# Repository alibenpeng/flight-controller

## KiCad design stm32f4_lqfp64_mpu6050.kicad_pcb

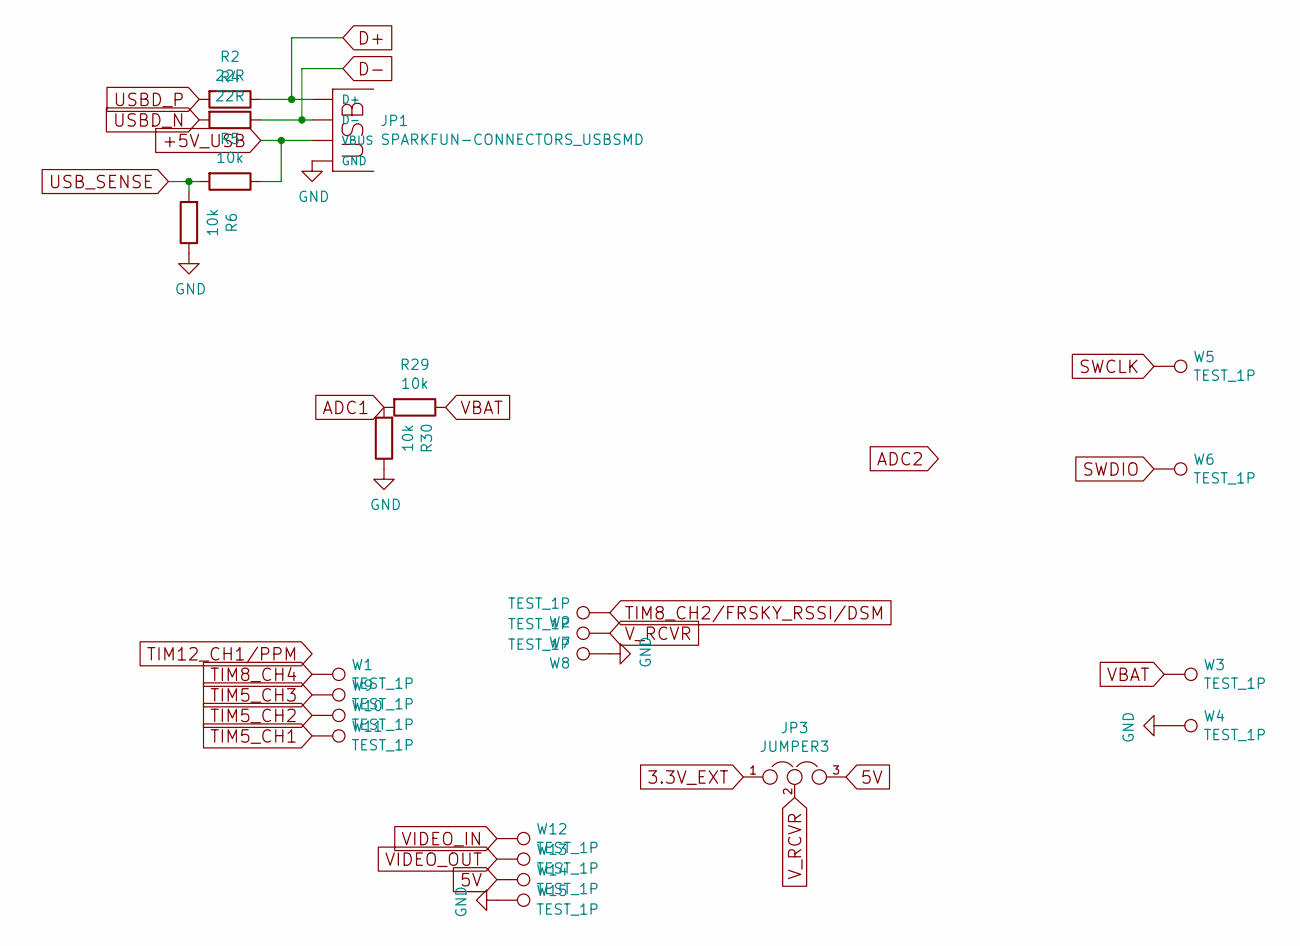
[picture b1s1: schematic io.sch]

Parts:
JP1: SPARKFUN-CONNECTORS_USBSMD; micro_usb
JP3: JUMPER3; SPARKFUN-PASSIVES_PAD-JUMPER-3-2OF3_NC_BY_PASTE_YES_SILK_FU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
R2, R4: 22R; R_0402
R5, R6, R29, R30: 10k; R_0402
W1, W2, W7, W8, W9, W10, W11, W12, W13, W14, W15: TEST_1P; pad_2x1.5mm
W3, W4: TEST_1P; battery_pad
W5, W6: TEST_1P; pad_round_1mm

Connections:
3.3V_EXT: JP3.1; also elsewhere on the board
5V: JP3.3, W14.1; also elsewhere on the board
+5V_USB: JP1.VBUS, R5.1; also elsewhere on the board
ADC1: R29.2, R30.2; also elsewhere on the board
D+: JP1.D+, R2.1
D-: JP1.D-, R4.1
SWCLK: W5.1; also elsewhere on the board
SWDIO: W6.1; also elsewhere on the board
TIM5_CH1: W11.1; also elsewhere on the board
TIM5_CH2: W10.1; also elsewhere on the board
TIM5_CH3: W9.1; also elsewhere on the board
TIM8_CH2/FRSKY_RSSI/DSM: W2.1; also elsewhere on the board
TIM8_CH4: W1.1; also elsewhere on the board
USBD_N: R4.2; also elsewhere on the board
USBD_P: R2.2; also elsewhere on the board
USB_SENSE: R5.2, R6.2; also elsewhere on the board
VIDEO_IN: W12.1; also elsewhere on the board
VIDEO_OUT: W13.1; also elsewhere on the board
V_RCVR: JP3.2, W7.1

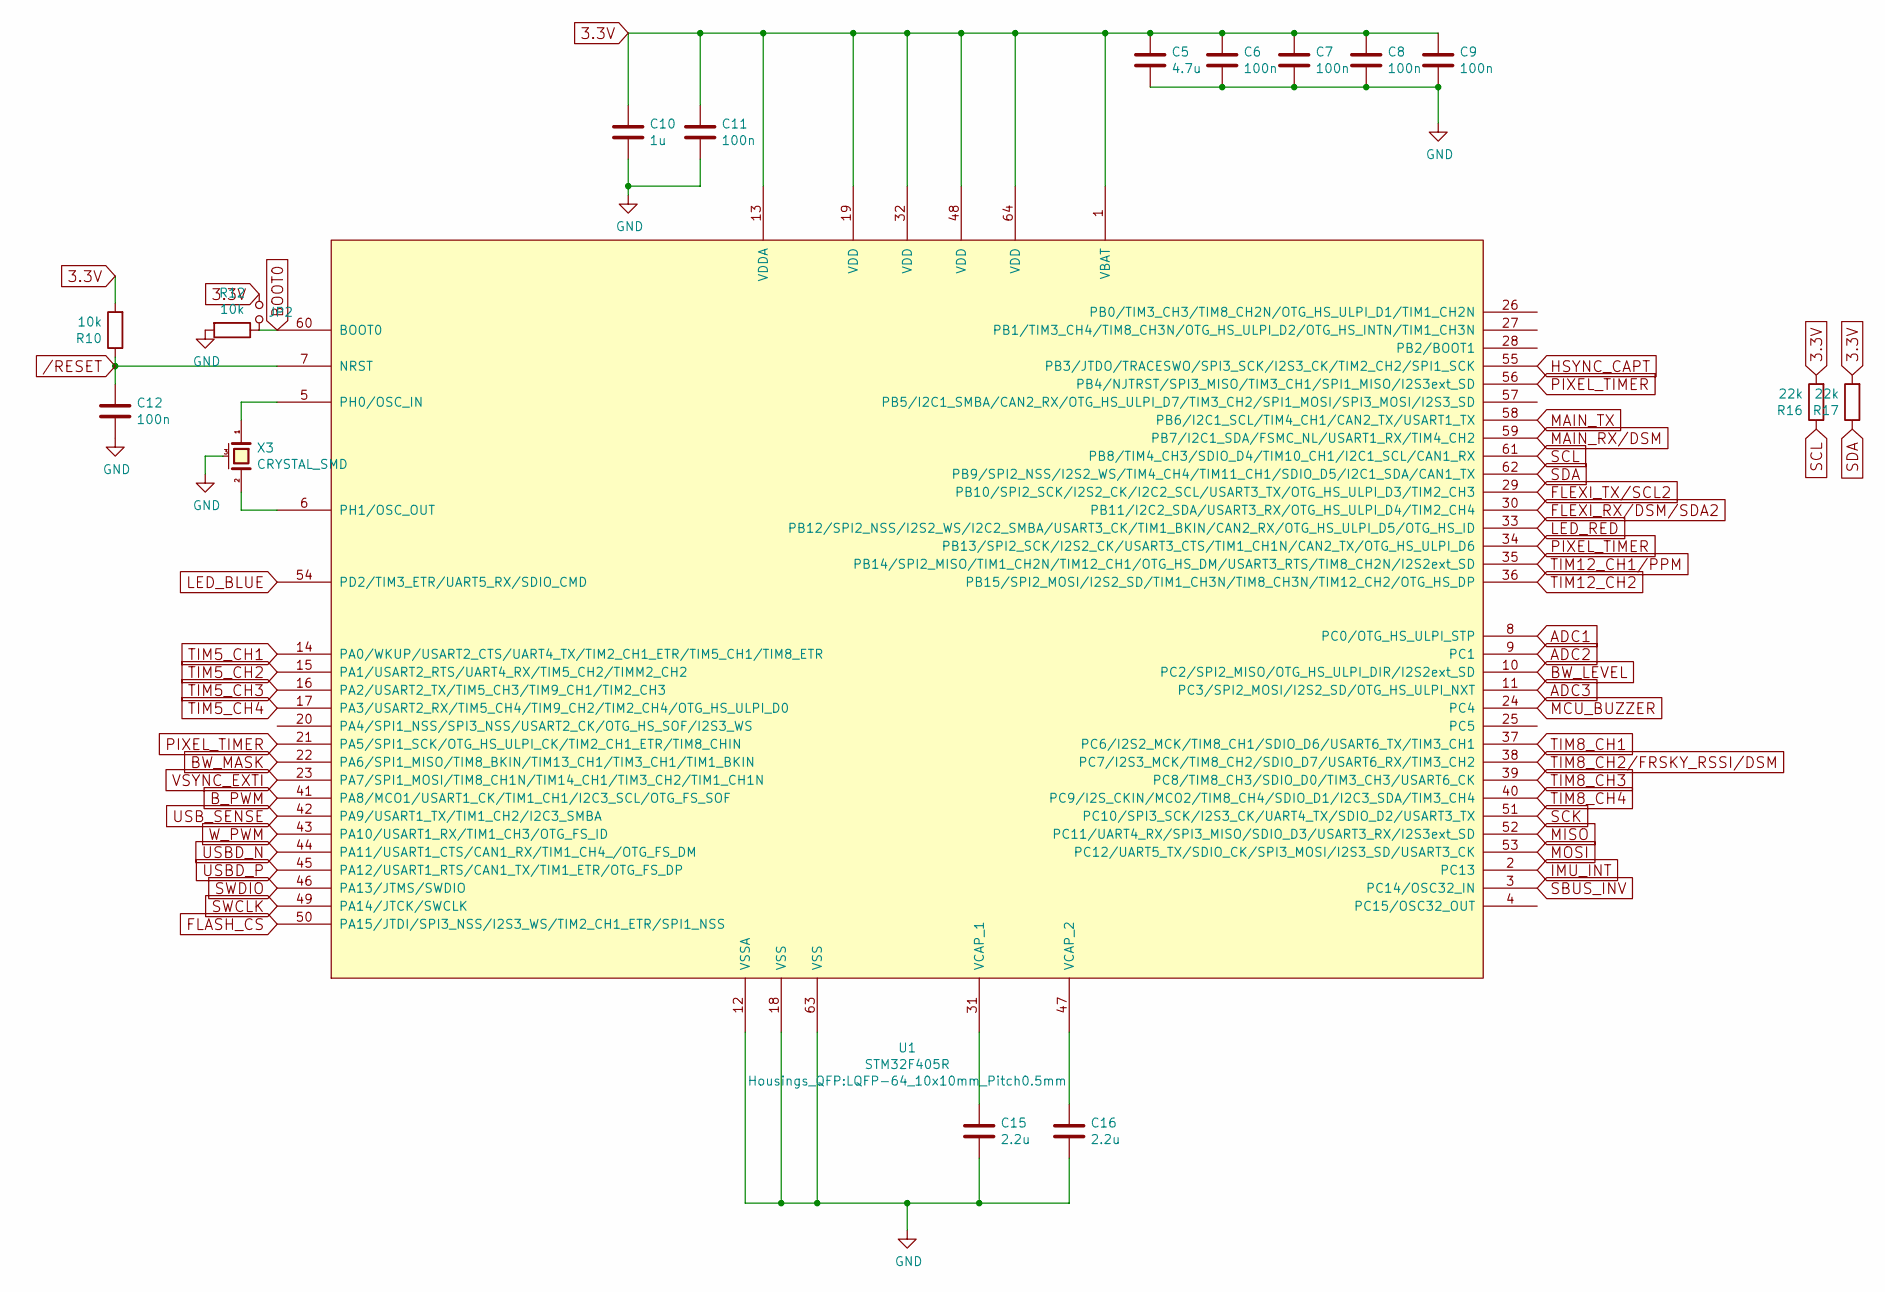
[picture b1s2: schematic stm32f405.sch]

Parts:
C5: 4.7u; C_0603
C6, C7, C8, C9, C11, C12: 100n; C_0402
C10: 1u; C_0402
C15, C16: 2.2u; C_0603
JP2: Jumper_NO_Small; ALIS-CUSTOM-PARTS_PAD-JUMPER-2-NO_YES_SILK
R10, R12: 10k; R_0402
R16, R17: 22k; R_0402
U1: STM32F405R; LQFP-64_10x10mm_Pitch0.5mm
X3: CRYSTAL_SMD; Resonator_3.2x1.3mm

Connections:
3.3V: C5.1, C6.1, C7.1, C8.1, C9.1, C10.1, C11.1, JP2.1, R10.2, R16.2, R17.2, U1.1 (VBAT), U1.13 (VDDA), U1.19 (VDD), U1.32 (VDD), U1.48 (VDD), U1.64 (VDD); also elsewhere on the board
/RESET: C12.1, R10.1, U1.7 (NRST)
ADC1: U1.8 (PC0/OTG_HS_ULPI_STP); also elsewhere on the board
ADC2: U1.9 (PC1)
ADC3: U1.11 (PC3/SPI2_MOSI/I2S2_SD/OTG_HS_ULPI_NXT)
BOOT0: JP2.2, R12.1, U1.60 (BOOT0); also elsewhere on the board
BW_LEVEL: U1.10 (PC2/SPI2_MISO/OTG_HS_ULPI_DIR/I2S2ext_SD); also elsewhere on the board
BW_MASK: U1.22 (PA6/SPI1_MISO/TIM8_BKIN/TIM13_CH1/TIM3_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); also elsewhere on the board
B_PWM: U1.41 (PA8/MCO1/USART1_CK/TIM1_CH1/I2C3_SCL/OT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); also elsewhere on the board
FLASH_CS: U1.50 (PA15/JTDI/SPI3_NSS/I2S3_WS/TIM2_CH1_ETR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)
FLEXI_RX/DSM/SDA2: U1.30 (PB11/I2C2_SDA/USART3_RX/OTG_HS_ULPI_D4/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)
FLEXI_TX/SCL2: U1.29 (PB10/SPI2_SCK/I2S2_CK/I2C2_SCL/USART3_T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)
HSYNC_CAPT: U1.55 (PB3/JTDO/TRACESWO/SPI3_SCK/I2S3_CK/TIM2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); also elsewhere on the board
IMU_INT: U1.2 (PC13); also elsewhere on the board
LED_BLUE: U1.54 (PD2/TIM3_ETR/UART5_RX/SDIO_CMD); also elsewhere on the board
LED_RED: U1.33 (PB12/SPI2_NSS/I2S2_WS/I2C2_SMBA/USART3_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)
MAIN_RX/DSM: U1.59 (PB7/I2C1_SDA/FSMC_NL/USART1_RX/TIM4_CH2)
MAIN_TX: U1.58 (PB6/I2C1_SCL/TIM4_CH1/CAN2_TX/USART1_TX)
MCU_BUZZER: U1.24 (PC4)
MISO: U1.52 (PC11/UART4_RX/SPI3_MISO/SDIO_D3/USART3_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)
MOSI: U1.53 (PC12/UART5_TX/SDIO_CK/SPI3_MOSI/I2S3_SD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)
unnamed: C15.1, U1.31 (VCAP_1)
unnamed: C16.1, U1.47 (VCAP_2)
unnamed: U1.5 (PH0/OSC_IN), X3.1
unnamed: U1.6 (PH1/OSC_OUT), X3.2
PIXEL_TIMER: U1.21 (PA5/SPI1_SCK/OTG_HS_ULPI_CK/TIM2_CH1_ET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), U1.34 (PB13/SPI2_SCK/I2S2_CK/USART3_CTS/TIM1_C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), U1.56 (PB4/NJTRST/SPI3_MISO/TIM3_CH1/SPI1_MISO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)
SBUS_INV: U1.3 (PC14/OSC32_IN)
SCK: U1.51 (PC10/SPI3_SCK/I2S3_CK/UART4_TX/SDIO_D2/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)
SCL: R16.1, U1.61 (PB8/TIM4_CH3/SDIO_D4/TIM10_CH1/I2C1_SCL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); also elsewhere on the board
SDA: R17.1, U1.62 (PB9/SPI2_NSS/I2S2_WS/TIM4_CH4/TIM11_CH1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); also elsewhere on the board
SWCLK: U1.49 (PA14/JTCK/SWCLK); also elsewhere on the board
SWDIO: U1.46 (PA13/JTMS/SWDIO); also elsewhere on the board
TIM5_CH1: U1.14 (PA0/WKUP/USART2_CTS/UART4_TX/TIM2_CH1_E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); also elsewhere on the board
TIM5_CH2: U1.15 (PA1/USART2_RTS/UART4_RX/TIM5_CH2/TIMM2_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); also elsewhere on the board
TIM5_CH3: U1.16 (PA2/USART2_TX/TIM5_CH3/TIM9_CH1/TIM2_CH3); also elsewhere on the board
TIM5_CH4: U1.17 (PA3/USART2_RX/TIM5_CH4/TIM9_CH2/TIM2_CH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)
TIM8_CH1: U1.37 (PC6/I2S2_MCK/TIM8_CH1/SDIO_D6/USART6_TX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)
TIM8_CH2/FRSKY_RSSI/DSM: U1.38 (PC7/I2S3_MCK/TIM8_CH2/SDIO_D7/USART6_RX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); also elsewhere on the board
TIM8_CH3: U1.39 (PC8/TIM8_CH3/SDIO_D0/TIM3_CH3/USART6_CK)
TIM8_CH4: U1.40 (PC9/I2S_CKIN/MCO2/TIM8_CH4/SDIO_D1/I2C3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); also elsewhere on the board
TIM12_CH1/PPM: U1.35 (PB14/SPI2_MISO/TIM1_CH2N/TIM12_CH1/OTG_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)
TIM12_CH2: U1.36 (PB15/SPI2_MOSI/I2S2_SD/TIM1_CH3N/TIM8_C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)
USBD_N: U1.44 (PA11/USART1_CTS/CAN1_RX/TIM1_CH4_/OTG_F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); also elsewhere on the board
USBD_P: U1.45 (PA12/USART1_RTS/CAN1_TX/TIM1_ETR/OTG_FS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); also elsewhere on the board
USB_SENSE: U1.42 (PA9/USART1_TX/TIM1_CH2/I2C3_SMBA); also elsewhere on the board
VSYNC_EXTI: U1.23 (PA7/SPI1_MOSI/TIM8_CH1N/TIM14_CH1/TIM3_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); also elsewhere on the board
W_PWM: U1.43 (PA10/USART1_RX/TIM1_CH3/OTG_FS_ID); also elsewhere on the board

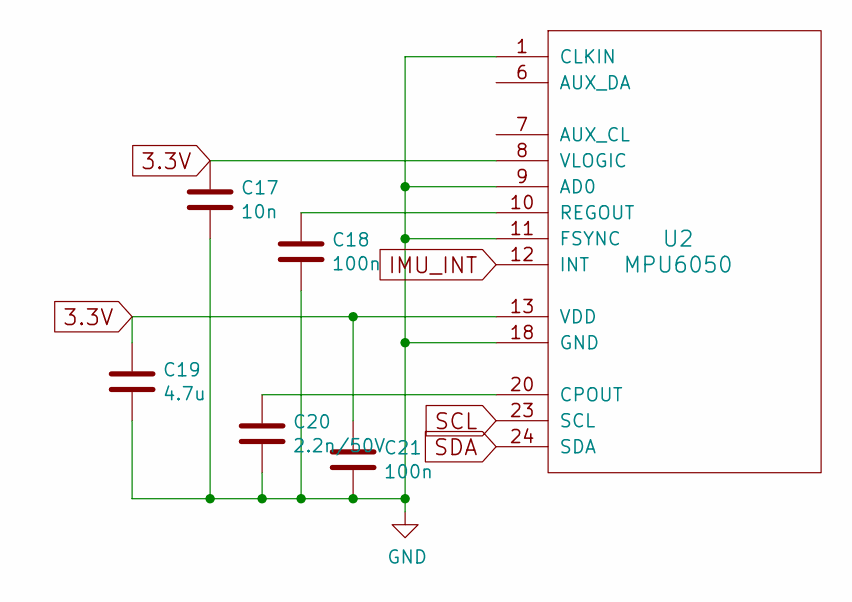
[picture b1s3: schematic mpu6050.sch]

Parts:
C17: 10n; C_0402
C18, C21: 100n; C_0402
C19: 4.7u; C_0603
C20: 2.2n/50V; C_0402
U2: MPU6050; QFN-24-noEP_4x4mm_Pitch0.5mm

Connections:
3.3V: C17.1, C19.1, C21.1, U2.8 (VLOGIC), U2.13 (VDD); also elsewhere on the board
IMU_INT: U2.12 (INT); also elsewhere on the board
unnamed: C18.1, U2.10 (REGOUT)
unnamed: C20.1, U2.20 (CPOUT)
SCL: U2.23 (SCL); also elsewhere on the board
SDA: U2.24 (SDA); also elsewhere on the board

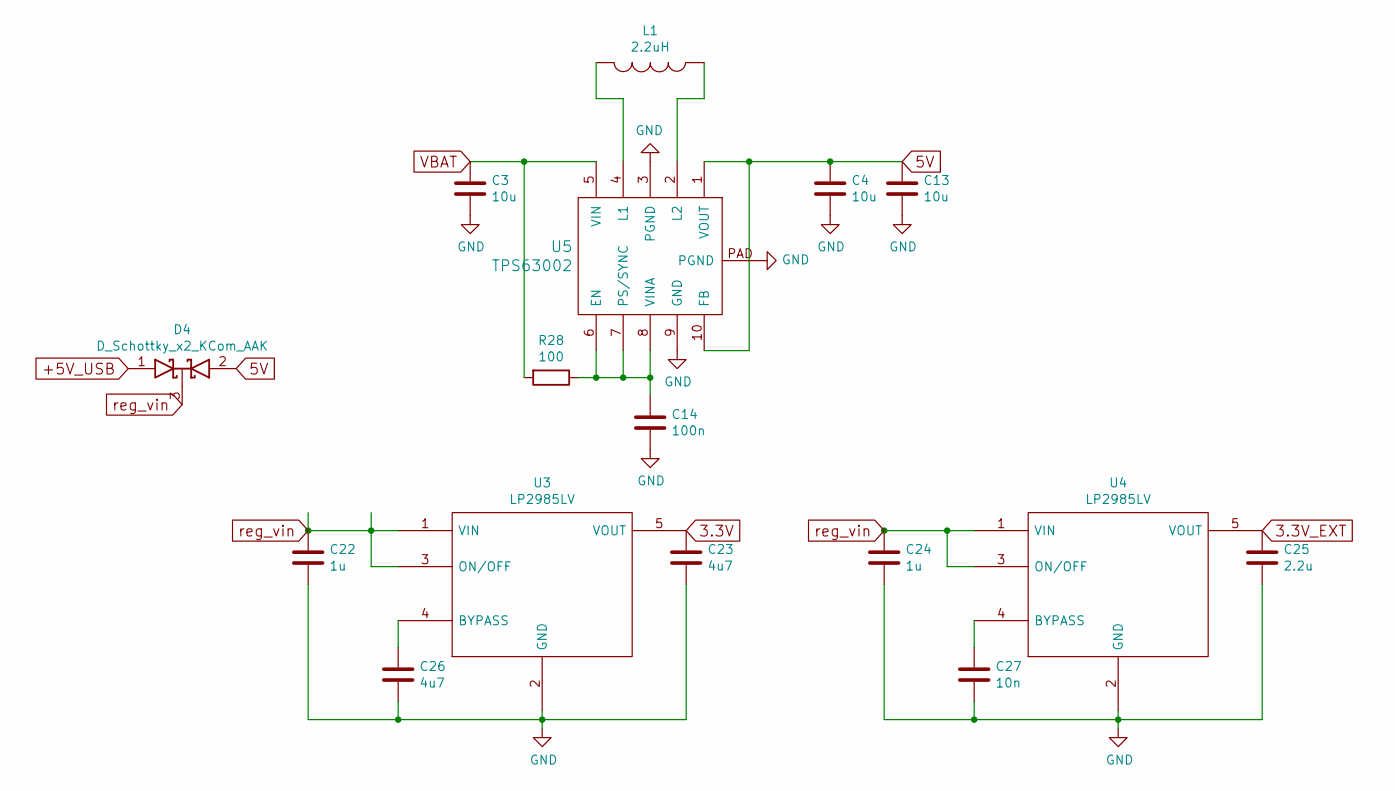
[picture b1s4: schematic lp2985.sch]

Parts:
C3, C4, C13: 10u; C_0603
C14: 100n; C_0402
C22, C24: 1u; C_0402
C23, C26: 4u7; C_0603
C25: 2.2u; C_0603
C27: 10n; C_0402
D4: D_Schottky_x2_KCom_AAK; SOT-23
L1: 2.2uH; Choke_SMD_Taiyo_NR3015
R28: 100; R_0402
U3, U4: LP2985LV; SOT-23-5
U5: TPS63002

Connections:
3.3V: C23.1, U3.5 (VOUT); also elsewhere on the board
3.3V_EXT: C25.1, U4.5 (VOUT); also elsewhere on the board
5V: C4.1, C13.1, D4.2 (A), U5.1 (VOUT), U5.10 (FB); also elsewhere on the board
+5V_USB: D4.1 (A); also elsewhere on the board
unnamed: C14.1, R28.1, U5.6 (EN), U5.7 (PS/SYNC), U5.8 (VINA)
unnamed: C26.1, U3.4 (BYPASS)
unnamed: C27.1, U4.4 (BYPASS)
unnamed: L1.1, U5.2 (L2)
unnamed: L1.2, U5.4 (L1)
reg_vin: C22.1, C24.1, D4.3 (K), U3.1 (VIN), U3.3 (ON/OFF), U4.1 (VIN), U4.3 (ON/OFF)

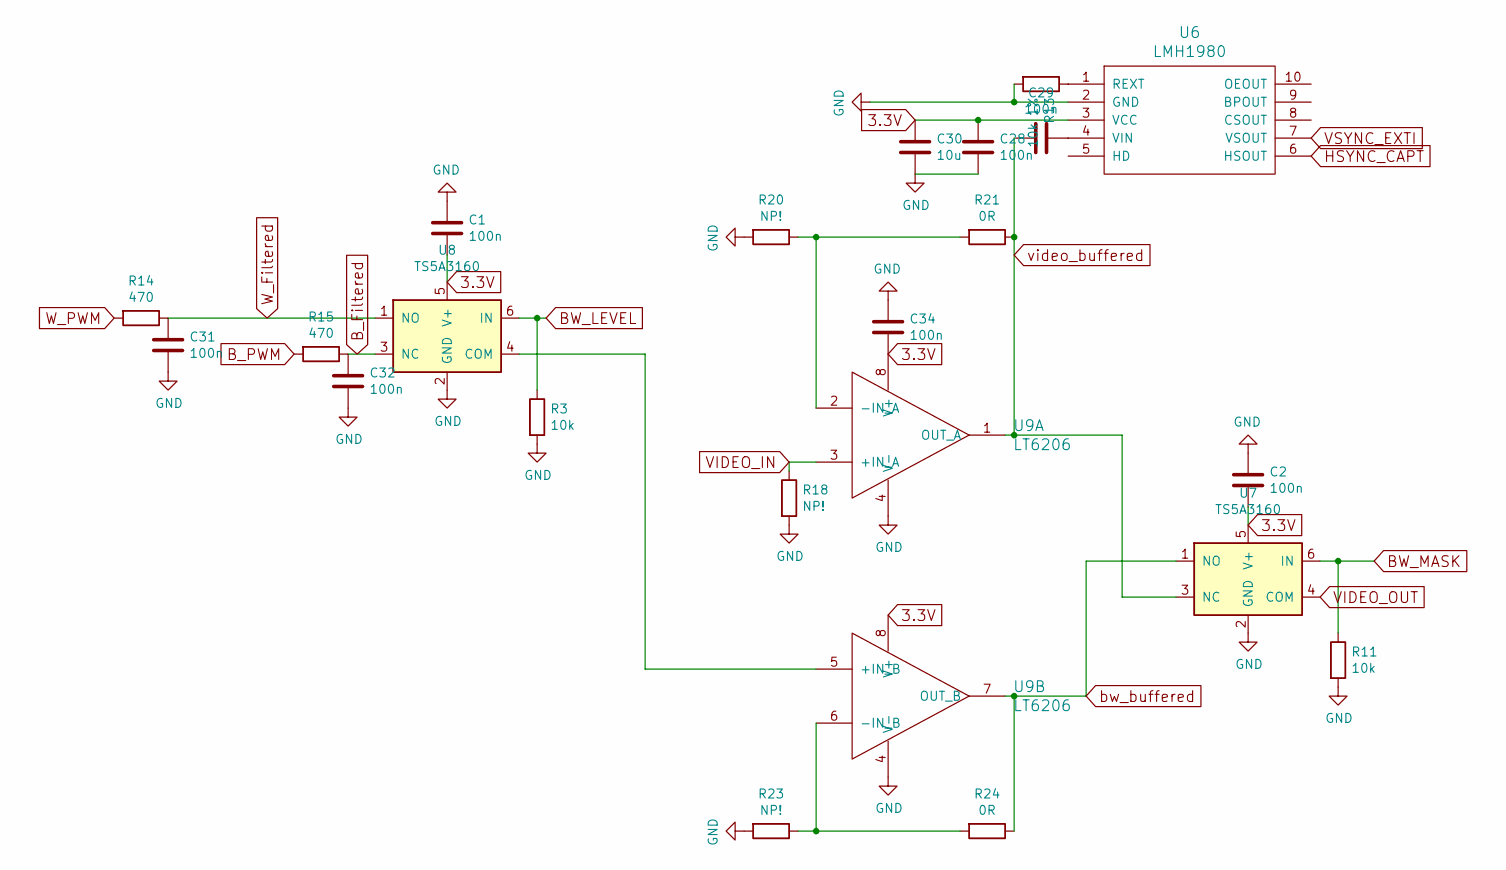
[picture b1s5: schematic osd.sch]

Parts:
C1, C2, C28, C29, C31, C32, C34: 100n; C_0402
C30: 10u; C_0603
R3, R11: 10k; R_0402
R13: 10k 1%; R_0402
R14, R15: 470; R_0402
R18, R20, R23: NP!; R_0402
R21, R24: 0R; R_0402
U6: LMH1980; TSSOP-10_3x3mm_Pitch0.5mm
U7, U8: TS5A3160; SC-70-6
U9: LT6206; MSOP-8_3x3mm_Pitch0.65mm

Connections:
3.3V: C1.2, C2.2, C28.1, C30.1, C34.2, U6.3 (VCC), U7.5 (V+), U8.5 (V+), U9.8 (V+); also elsewhere on the board
BW_LEVEL: R3.1, U8.6 (IN); also elsewhere on the board
BW_MASK: R11.1, U7.6 (IN); also elsewhere on the board
B_Filtered: C32.1, R15.1, U8.3 (NC)
B_PWM: R15.2; also elsewhere on the board
HSYNC_CAPT: U6.6 (HSOUT); also elsewhere on the board
unnamed: C29.1, U6.4 (VIN)
unnamed: R13.1, U6.1 (REXT)
unnamed: R20.1, R21.2, U9.2 (-IN_A)
unnamed: R23.1, R24.2, U9.6 (-IN_B)
unnamed: U8.4 (COM), U9.5 (+IN_B)
VIDEO_IN: R18.1, U9.3 (+IN_A); also elsewhere on the board
VIDEO_OUT: U7.4 (COM); also elsewhere on the board
VSYNC_EXTI: U6.7 (VSOUT); also elsewhere on the board
W_Filtered: C31.1, R14.1, U8.1 (NO)
W_PWM: R14.2; also elsewhere on the board
bw_buffered: R24.1, U7.1 (NO), U9.7 (OUT_B)
video_buffered: C29.2, R21.1, U7.3 (NC), U9.1 (OUT_A)

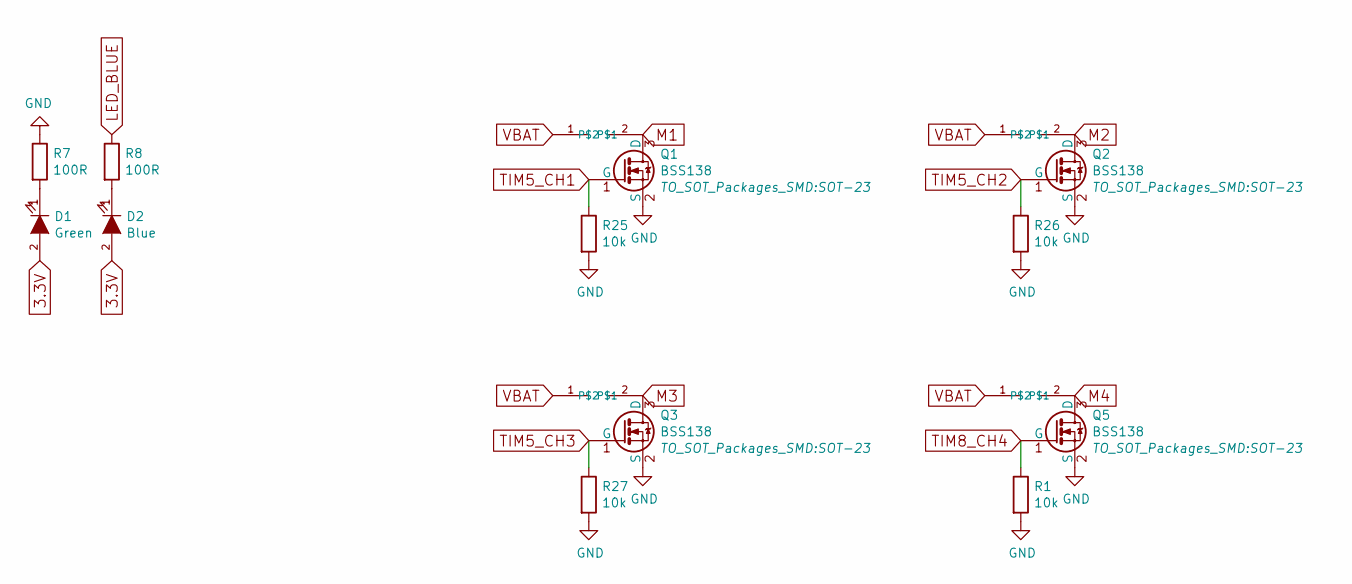
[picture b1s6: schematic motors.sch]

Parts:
D1: Green; LED-0603
D2: Blue; LED-0603
M1, M2, M3, M5: ALIS-CUSTOM-PARTS_POWERPADS; motor_pads
Q1, Q2, Q3, Q5: BSS138; SOT-23
R1, R25, R26, R27: 10k; R_0402
R7, R8: 100R; R_0402

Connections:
3.3V: D1.2 (A), D2.2 (A); also elsewhere on the board
LED_BLUE: R8.1; also elsewhere on the board
M1: M1.2, Q1.3 (D)
M2: M2.2, Q2.3 (D)
M3: M3.2, Q3.3 (D)
M4: M5.2, Q5.3 (D)
unnamed: D1.1 (K), R7.2
unnamed: D2.1 (K), R8.2
TIM5_CH1: Q1.1 (G), R25.1; also elsewhere on the board
TIM5_CH2: Q2.1 (G), R26.1; also elsewhere on the board
TIM5_CH3: Q3.1 (G), R27.1; also elsewhere on the board
TIM8_CH4: Q5.1 (G), R1.1; also elsewhere on the board

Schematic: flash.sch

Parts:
C3: 2.2u; C_0603
U5: W25Q80BV; SOIJ-8_5.3x5.3mm_Pitch1.27mm

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
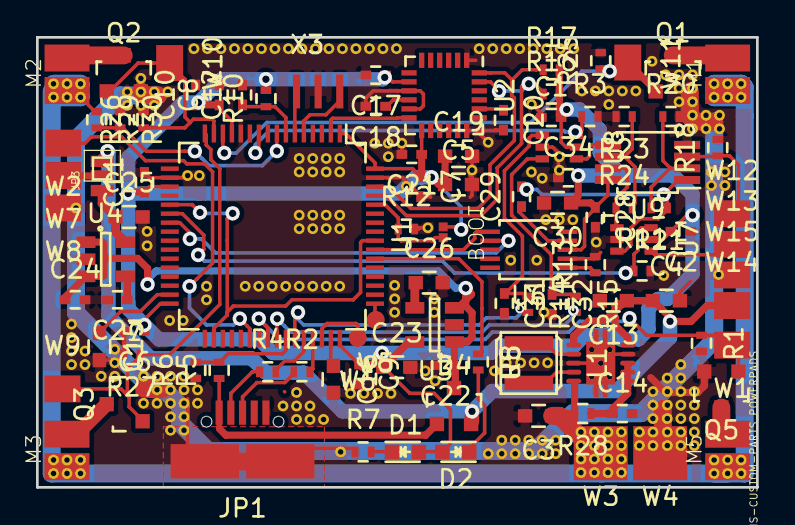
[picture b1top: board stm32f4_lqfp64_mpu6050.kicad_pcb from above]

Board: 2 copper layers, 40.0 x 25.0 mm, 100 parts (0 on the bottom side), 62 nets.

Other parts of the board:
BOOT: ALIS-CUSTOM-PARTS_PAD-JUMPER-2-NO_YES_SILK

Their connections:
3.3V: BOOT.1; also elsewhere on the board
BOOT0: BOOT.2; also elsewhere on the board

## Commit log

2016-01-15 moved schematic blocks to hierarchical sheets
2016-03-08 added lots of stuff
2016-04-06 added i2c pullups, IMU int and USB sense
2016-04-06 added IMU int and USB sense in schematic
2016-04-08 began to add support for video overlay
2016-04-09 re-sorted motors
2016-04-10 changed some netnames
2016-05-01 OSD running on breadboard
2016-05-04 power traces routed
2016-05-05 routing done except for ground, but ugly
2016-05-05 best relative placement
2016-05-06 first pass routing complete
2016-05-06 second pass routing complete
2016-05-06 re-routed upper three video signals
2016-05-06 looks better than the rcexplorer naze32
2016-05-06 improved a few ground connections
2016-05-06 deleted the ground pad under the mpu6050
2016-05-15 added I2C pullups and pulled MPU6050 AD0 to GND (DOH)
2016-06-04 added lt6206 and replaced lm1881 with lmh1980. routing unfinished.
2016-06-14 routing finished - essential signals only
2016-08-21 minor changes
2016-09-07 fixing switch polarity
2016-09-14 fixed video opamp and output switch circuit, removed line termination resistors
2016-09-22 fixed opamp circuit and some cosmetics

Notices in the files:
stm32f4_lqfp64_mpu6050.kicad_pcb:
© Alexander Tuxen 2016
